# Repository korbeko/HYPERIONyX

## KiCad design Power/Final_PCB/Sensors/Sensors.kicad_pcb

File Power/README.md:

When loading the KiCad project, the components directory must be adjusted based on where you copy the repository.
To fix:
1. Select configure paths in the project window.
2. Select name: COMPONENTS and click folder icon to change the path to wherever the components folder is.

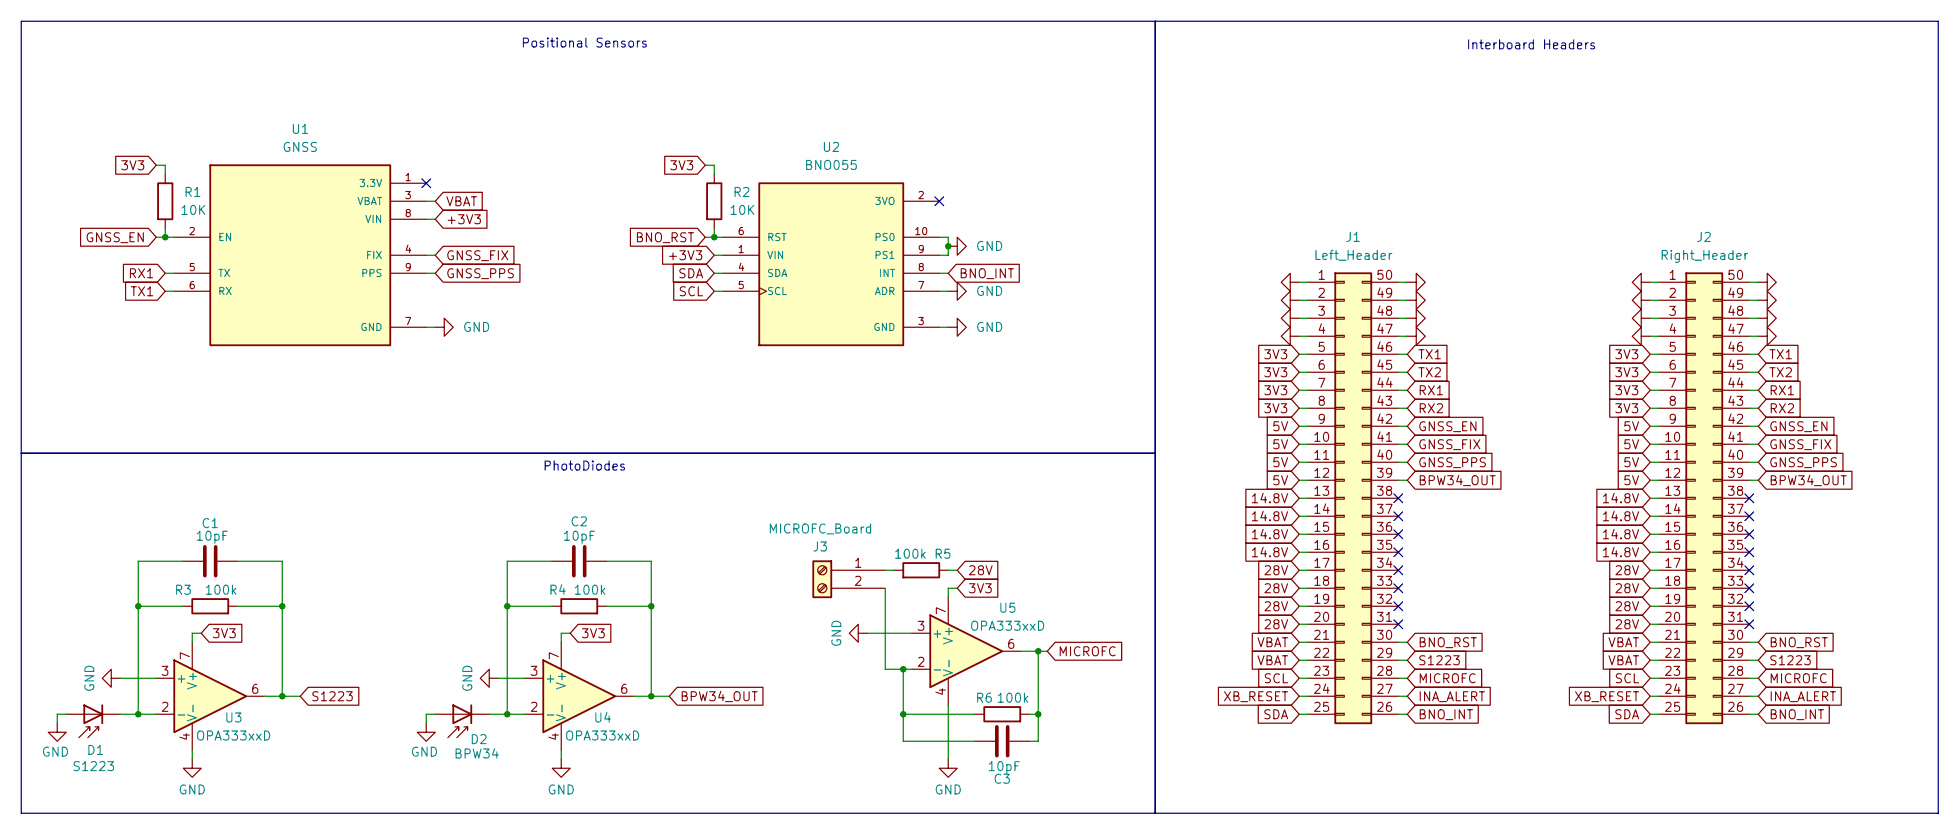
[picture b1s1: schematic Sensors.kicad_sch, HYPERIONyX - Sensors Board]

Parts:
C1, C2, C3: 10pF; C_Disc_D3.0mm_W1.6mm_P2.50mm
D1: S1223; PinHeader_1x02_P2.54mm_Vertical
D2: BPW34; PinHeader_1x02_P2.54mm_Vertical
J1: Left_Header; PinHeader_2x25_P2.54mm_Vertical
J2: Right_Header; PinHeader_2x25_P2.54mm_Vertical
J3: MICROFC_Board; PinHeader_1x02_P2.54mm_Vertical
R1, R2: 10K; R_Axial_DIN0207_L6.3mm_D2.5mm_P7.62mm_Horizontal
R3, R4, R5, R6: 100k; R_Axial_DIN0207_L6.3mm_D2.5mm_P7.62mm_Horizontal
U1: GNSS; PARTREV 2022-12-01
U2: BNO055; PARTREV N/A
U3, U4, U5: OPA333xxD; SOIC-8_3.9x4.9mm_P1.27mm

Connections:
3V3: J1.5, J1.6, J1.7, J1.8, J2.5, J2.6, J2.7, J2.8, R1.1, R2.1, U3.7 (V+), U4.7 (V+), U5.7 (V+)
5V: J1.9, J1.10, J1.11, J1.12, J2.9, J2.10, J2.11, J2.12
14.8V: J1.13, J1.14, J1.15, J1.16, J2.13, J2.14, J2.15, J2.16
28V: J1.17, J1.18, J1.19, J1.20, J2.17, J2.18, J2.19, J2.20, R5.1
+3V3: U1.8 (VIN), U2.1 (VIN)
BNO_INT: J1.26, J2.26, U2.8 (INT)
BNO_RST: J1.30, J2.30, R2.2, U2.6 (RST)
BPW34_OUT: C2.1, J1.39, J2.39, R4.2, U4.6
GND: D1.2 (A), D2.2 (A), J1.1, J1.2, J1.3, J1.4, J1.47, J1.48, J1.49, J1.50, J2.1, J2.2, J2.3, J2.4, J2.47, J2.48, J2.49, J2.50, U1.7 (GND), U2.3 (GND), U2.7 (ADR), U2.9 (PS1), U2.10 (PS0), U3.3 (+), U3.4 (V-), U4.3 (+), U4.4 (V-), U5.3 (+), U5.4 (V-)
GNSS_EN: J1.42, J2.42, R1.2, U1.2 (EN)
GNSS_FIX: J1.41, J2.41, U1.4 (FIX)
GNSS_PPS: J1.40, J2.40, U1.9 (PPS)
INA_ALERT: J1.27, J2.27
MICROFC: C3.1, J1.28, J2.28, R6.2, U5.6
unnamed: C1.2, D1.1 (K), R3.1, U3.2 (-)
unnamed: C2.2, D2.1 (K), R4.1, U4.2 (-)
unnamed: C3.2, J3.2 (SOUT), R6.1, U5.2 (-)
unnamed: J3.1 (VBIAS), R5.2
RX1: J1.44, J2.44, U1.5 (TX)
RX2: J1.43, J2.43
S1223: C1.1, J1.29, J2.29, R3.2, U3.6
SCL: J1.23, J2.23, U2.5 (SCL)
SDA: J1.25, J2.25, U2.4 (SDA)
TX1: J1.46, J2.46, U1.6 (RX)
TX2: J1.45, J2.45
VBAT: J1.21, J1.22, J2.21, J2.22, U1.3 (VBAT)
XB_RESET: J1.24, J2.24

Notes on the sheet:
Interboard Headers
Positional Sensors
PhotoDiodes

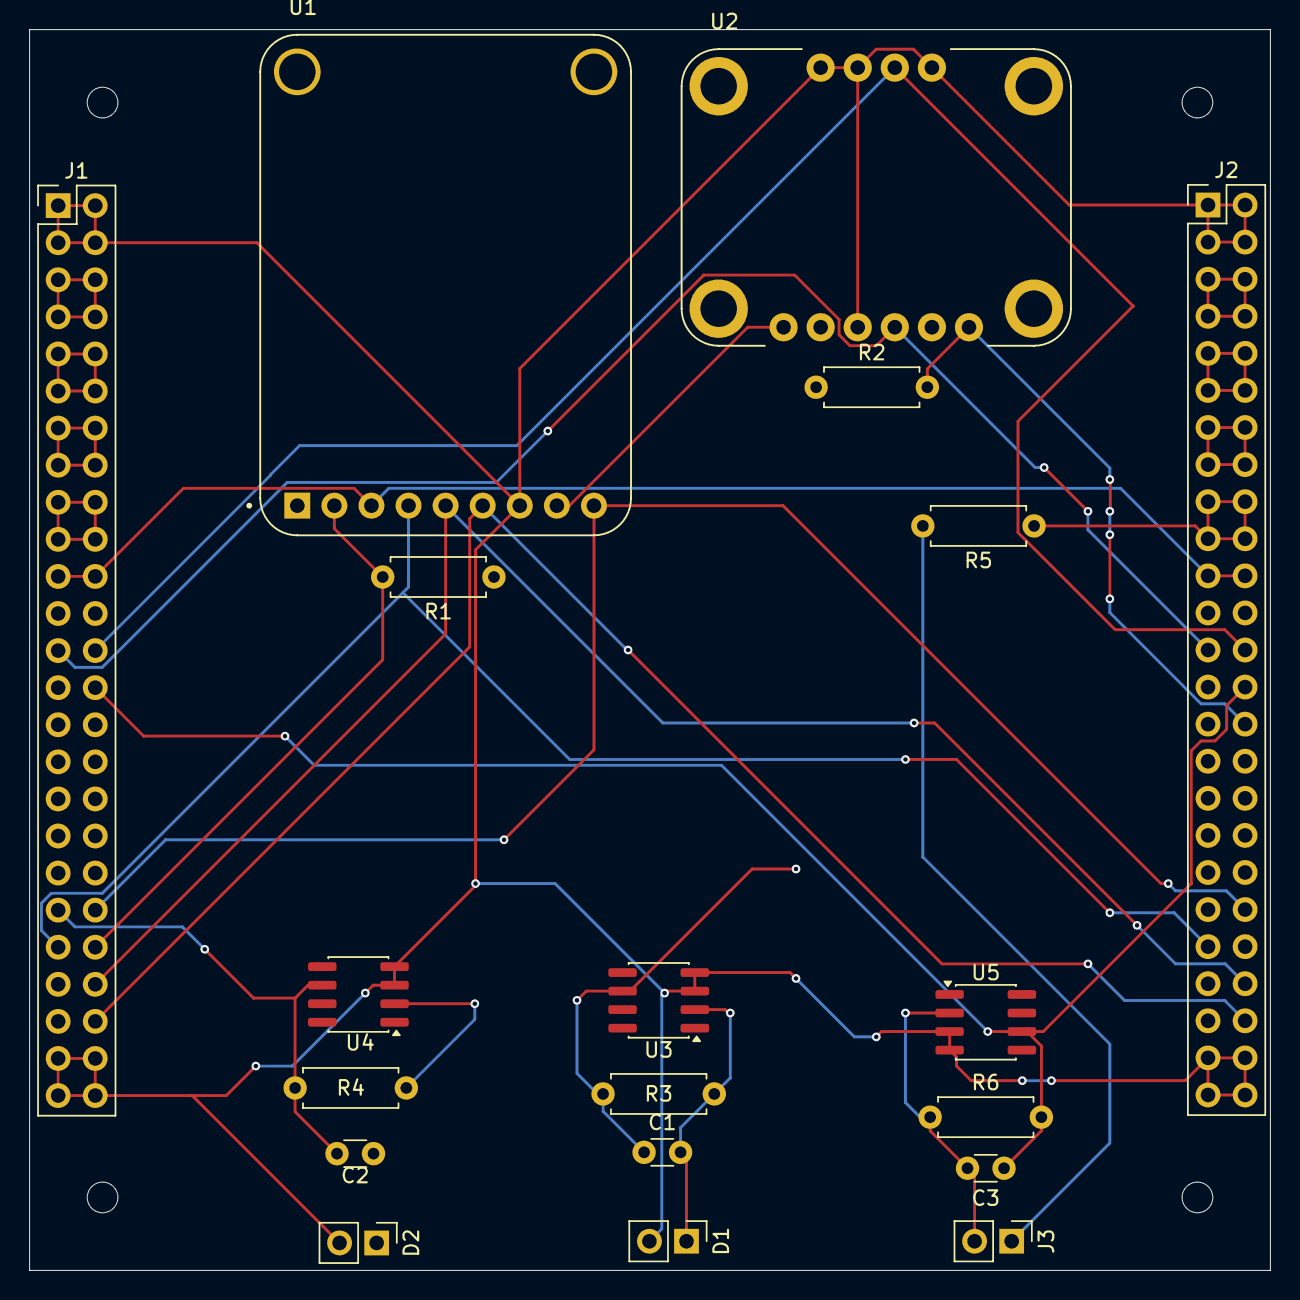
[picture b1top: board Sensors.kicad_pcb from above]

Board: 4 copper layers, 85.0 x 85.0 mm, 20 parts (1 on the bottom side), 27 nets.

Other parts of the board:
.: .; LOGO

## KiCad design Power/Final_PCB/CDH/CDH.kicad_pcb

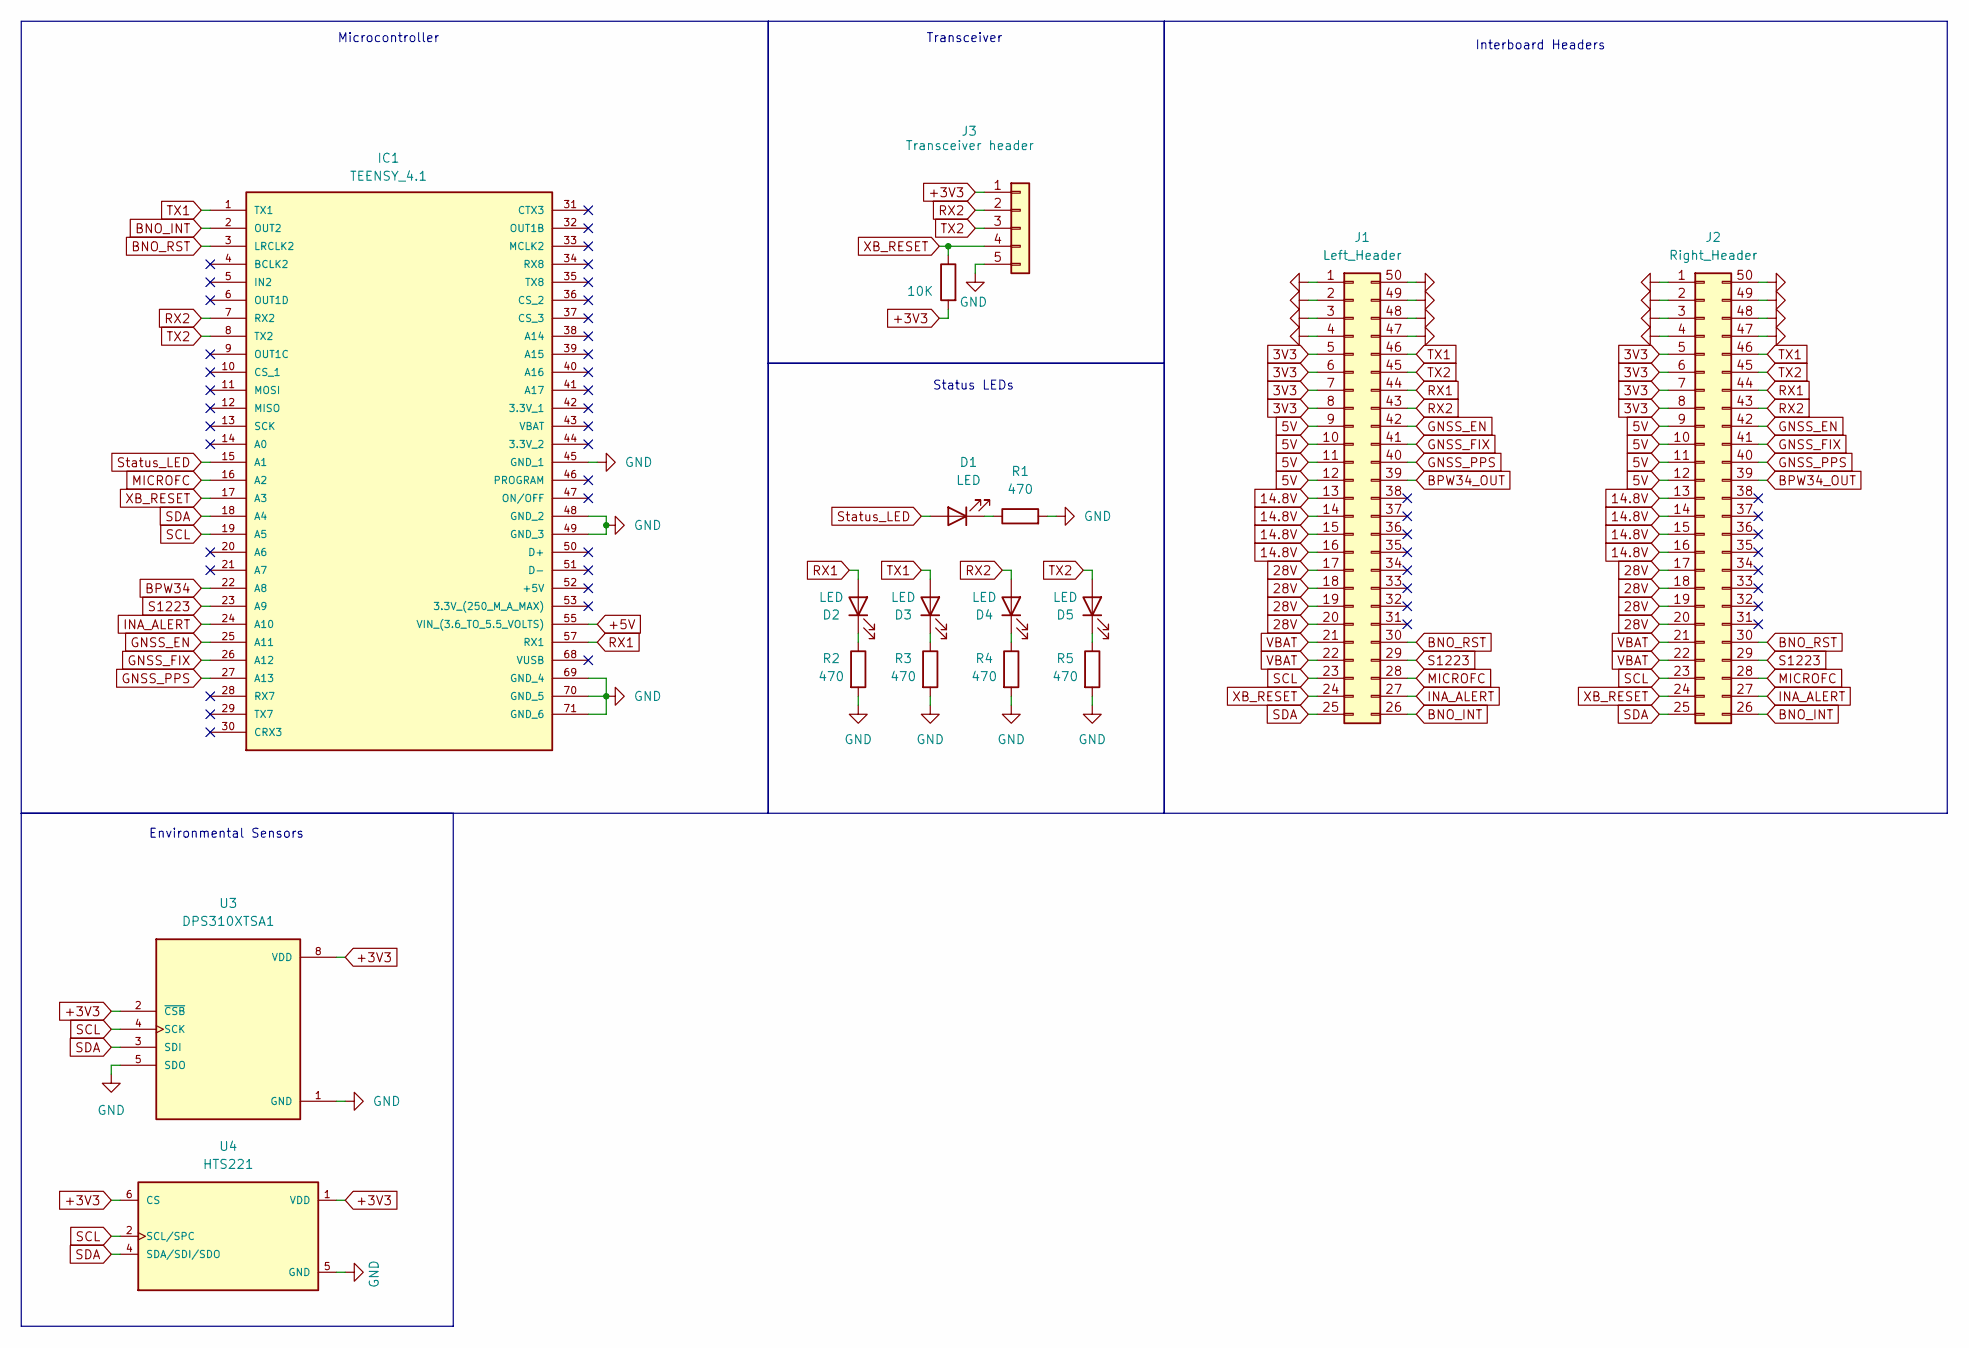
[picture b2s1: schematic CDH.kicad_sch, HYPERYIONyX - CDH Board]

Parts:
D1, D2, D3, D4, D5: LED; LED_D3.0mm
IC1: TEENSY_4.1; TEENSY41; Manufacturer_Part_Number TEENSY 4.1
J1: Left_Header; PinHeader_2x25_P2.54mm_Vertical
J2: Right_Header; PinHeader_2x25_P2.54mm_Vertical
J3: Transceiver header; PinHeader_1x05_P2.54mm_Vertical
R1, R2, R3, R4, R5: 470; R_Axial_DIN0207_L6.3mm_D2.5mm_P7.62mm_Horizontal
R10: 10K; R_Axial_DIN0207_L6.3mm_D2.5mm_P7.62mm_Horizontal
U3: DPS310XTSA1; DPS310_Breakout
U4: HTS221; HTS221_Breakout; PARTREV Rev 1

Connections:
3V3: J1.5, J1.6, J1.7, J1.8, J2.5, J2.6, J2.7, J2.8
5V: J1.9, J1.10, J1.11, J1.12, J2.9, J2.10, J2.11, J2.12
14.8V: J1.13, J1.14, J1.15, J1.16, J2.13, J2.14, J2.15, J2.16
28V: J1.17, J1.18, J1.19, J1.20, J2.17, J2.18, J2.19, J2.20
+3V3: J3.1, R10.2, U3.2 (~CSB), U3.8 (VDD), U4.1 (VDD), U4.6 (CS)
+5V: IC1.55 (VIN_(3.6_TO_5.5_VOLTS))
BNO_INT: IC1.2 (OUT2), J1.26, J2.26
BNO_RST: IC1.3 (LRCLK2), J1.30, J2.30
BPW34: IC1.22 (A8)
BPW34_OUT: J1.39, J2.39
GND: IC1.45 (GND_1), IC1.48 (GND_2), IC1.49 (GND_3), IC1.69 (GND_4), IC1.70 (GND_5), IC1.71 (GND_6), J1.1, J1.2, J1.3, J1.4, J1.47, J1.48, J1.49, J1.50, J2.1, J2.2, J2.3, J2.4, J2.47, J2.48, J2.49, J2.50, J3.5, R1.2, R2.2, R3.2, R4.2, R5.2, U3.1 (GND), U3.5 (SDO), U4.5 (GND)
GNSS_EN: IC1.25 (A11), J1.42, J2.42
GNSS_FIX: IC1.26 (A12), J1.41, J2.41
GNSS_PPS: IC1.27 (A13), J1.40, J2.40
INA_ALERT: IC1.24 (A10), J1.27, J2.27
MICROFC: IC1.16 (A2), J1.28, J2.28
unnamed: D1.1 (K), R1.1
unnamed: D2.1 (K), R2.1
unnamed: D3.1 (K), R3.1
unnamed: D4.1 (K), R4.1
unnamed: D5.1 (K), R5.1
RX1: D2.2 (A), IC1.57 (RX1), J1.44, J2.44
RX2: D4.2 (A), IC1.7 (RX2), J1.43, J2.43, J3.2
S1223: IC1.23 (A9), J1.29, J2.29
SCL: IC1.19 (A5), J1.23, J2.23, U3.4 (SCK), U4.2 (SCL/SPC)
SDA: IC1.18 (A4), J1.25, J2.25, U3.3 (SDI), U4.4 (SDA/SDI/SDO)
Status_LED: D1.2 (A), IC1.15 (A1)
TX1: D3.2 (A), IC1.1 (TX1), J1.46, J2.46
TX2: D5.2 (A), IC1.8 (TX2), J1.45, J2.45, J3.3
VBAT: J1.21, J1.22, J2.21, J2.22
XB_RESET: IC1.17 (A3), J1.24, J2.24, J3.4, R10.1

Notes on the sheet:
Interboard Headers
Microcontroller
Environmental Sensors
Status LEDs
Transceiver

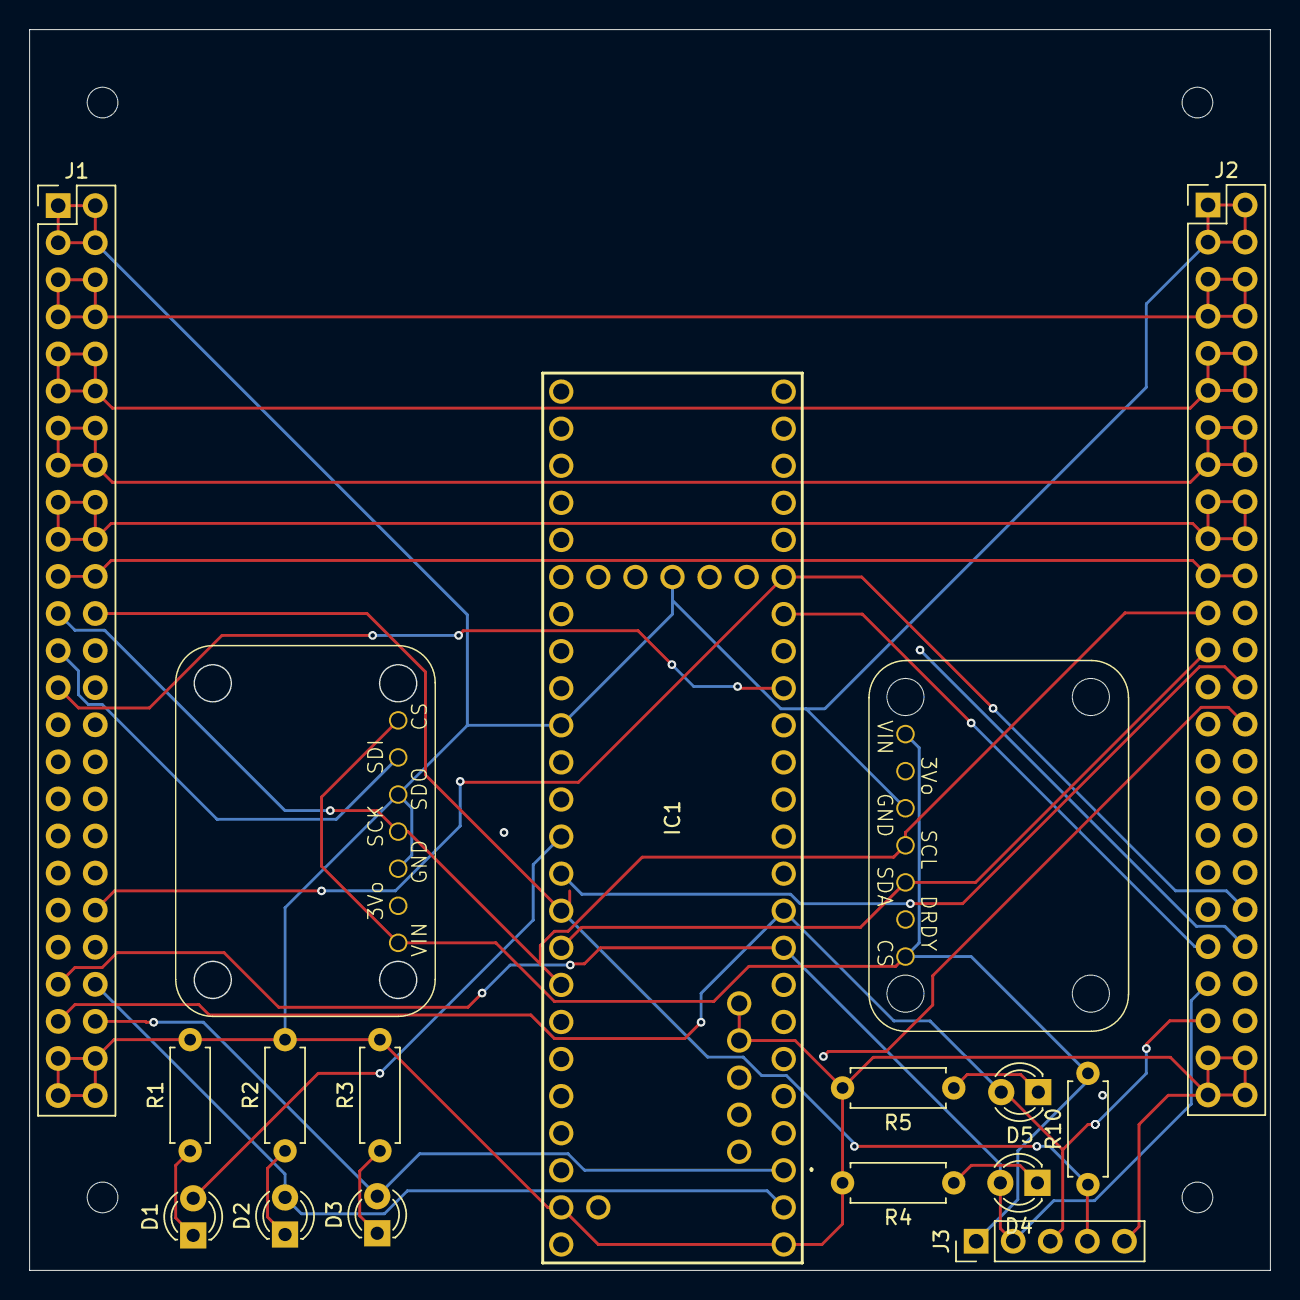
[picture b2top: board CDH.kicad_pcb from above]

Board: 4 copper layers, 84.9 x 84.9 mm, 18 parts (1 on the bottom side), 29 nets.

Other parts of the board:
.: .; LOGO

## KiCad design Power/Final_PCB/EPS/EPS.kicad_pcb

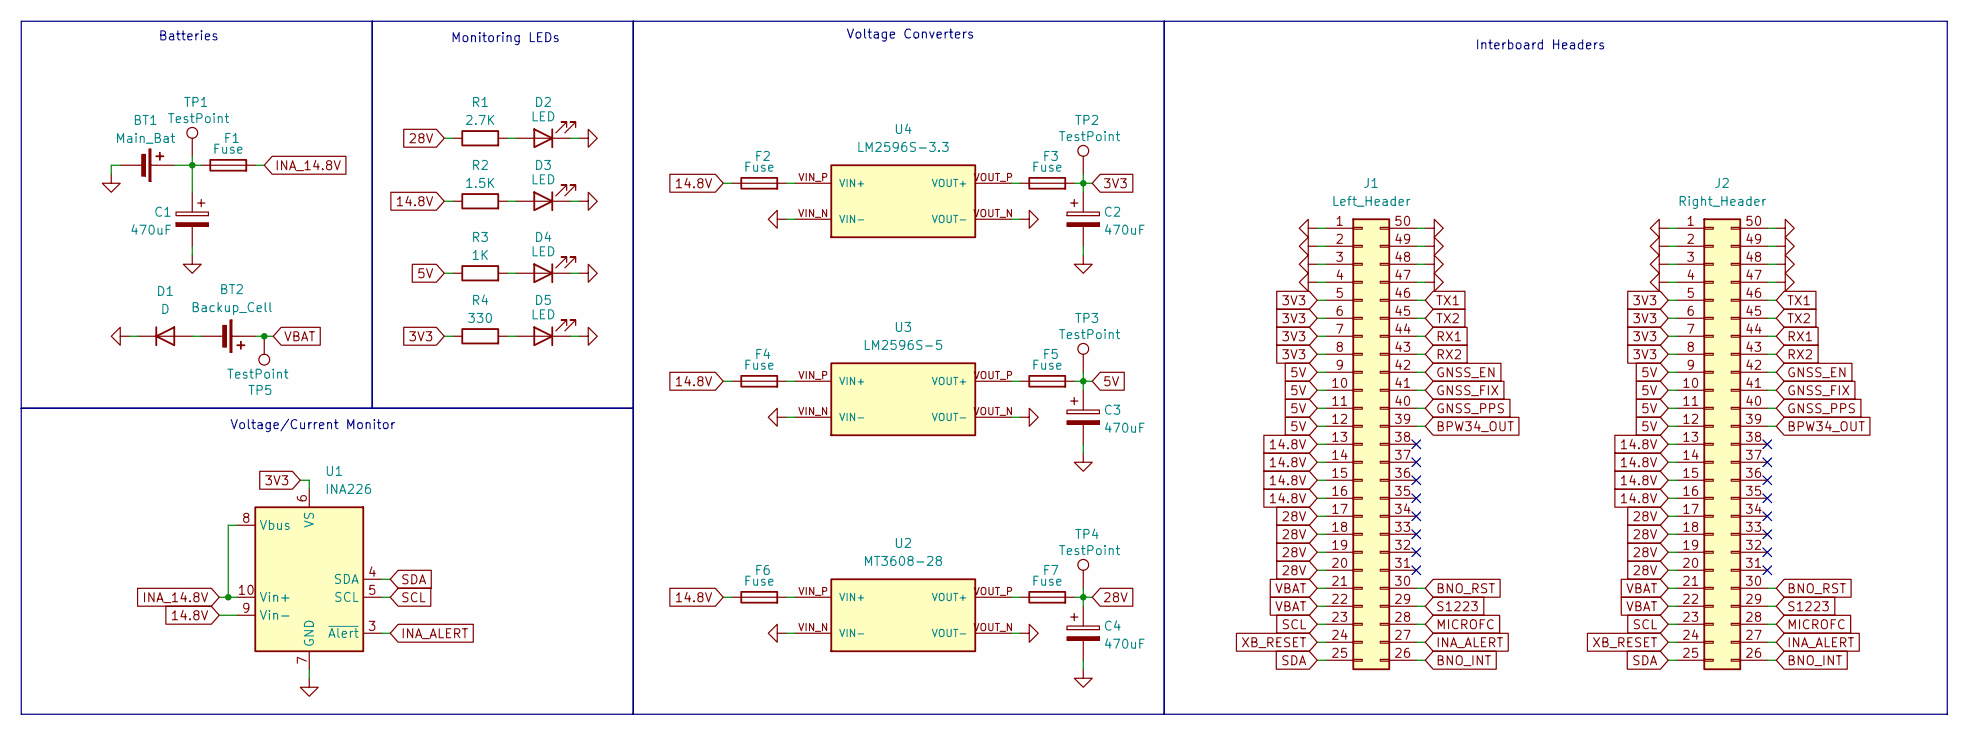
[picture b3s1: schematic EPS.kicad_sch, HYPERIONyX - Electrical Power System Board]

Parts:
BT1: Main_Bat; PinHeader_1x02_P2.54mm_Vertical
BT2: Backup_Cell; BatteryHolder_Multicomp_BC-2001_1x2032
C1, C2, C3, C4: 470uF; CP_Radial_D8.0mm_P3.50mm
D1: D; D_DO-15_P10.16mm_Horizontal
D2, D3, D4, D5: LED; LED_D3.0mm
F1, F2, F3, F4, F5, F6, F7: Fuse; Fuse_Blade_Mini_directSolder
J1: Left_Header; PinHeader_2x25_P2.54mm_Vertical
J2: Right_Header; PinHeader_2x25_P2.54mm_Vertical
R1: 2.7K; R_Axial_DIN0207_L6.3mm_D2.5mm_P7.62mm_Horizontal
R2: 1.5K; R_Axial_DIN0207_L6.3mm_D2.5mm_P7.62mm_Horizontal
R3: 1K; R_Axial_DIN0207_L6.3mm_D2.5mm_P7.62mm_Horizontal
R4: 330; R_Axial_DIN0207_L6.3mm_D2.5mm_P7.62mm_Horizontal
TP1, TP2, TP3, TP4, TP5: TestPoint; TestPoint_Loop_D2.50mm_Drill1.0mm
U1: INA226; INA_Breakout
U2: MT3608-28; MODULE_MT3608_DC-DC_STEP_UP_CONVERTER_2A_BOOSTER_MODULE
U3: LM2596S-5; LM2596_Breakout
U4: LM2596S-3.3; LM2596_Breakout

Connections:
3V3: C2.1, F3.2, J1.5, J1.6, J1.7, J1.8, J2.5, J2.6, J2.7, J2.8, R4.1, TP2.1 (1_1), U1.6 (VS)
5V: C3.1, F5.2, J1.9, J1.10, J1.11, J1.12, J2.9, J2.10, J2.11, J2.12, R3.1, TP3.1 (1_1)
14.8V: F2.1, F4.1, F6.1, J1.13, J1.14, J1.15, J1.16, J2.13, J2.14, J2.15, J2.16, R2.1, U1.9 (Vin-)
28V: C4.1, F7.2, J1.17, J1.18, J1.19, J1.20, J2.17, J2.18, J2.19, J2.20, R1.1, TP4.1 (1_1)
BNO_INT: J1.26, J2.26
BNO_RST: J1.30, J2.30
BPW34_OUT: J1.39, J2.39
GND: BT1.2 (-), C1.2, C2.2, C3.2, C4.2, D1.1 (K), D2.1 (K), D3.1 (K), D4.1 (K), D5.1 (K), J1.1, J1.2, J1.3, J1.4, J1.47, J1.48, J1.49, J1.50, J2.1, J2.2, J2.3, J2.4, J2.47, J2.48, J2.49, J2.50, U1.7 (GND), U2.VIN_N (VIN-), U2.VOUT_N (VOUT-), U3.VIN_N (VIN-), U3.VOUT_N (VOUT-), U4.VIN_N (VIN-), U4.VOUT_N (VOUT-)
GNSS_EN: J1.42, J2.42
GNSS_FIX: J1.41, J2.41
GNSS_PPS: J1.40, J2.40
INA_14.8V: F1.2, U1.8 (Vbus), U1.10 (Vin+)
INA_ALERT: J1.27, J2.27, U1.3 (~Alert)
MICROFC: J1.28, J2.28
unnamed: BT1.1 (+), C1.1, F1.1, TP1.1 (1_1)
unnamed: BT2.2 (-), D1.2 (A)
unnamed: D2.2 (A), R1.2
unnamed: D3.2 (A), R2.2
unnamed: D4.2 (A), R3.2
unnamed: D5.2 (A), R4.2
unnamed: F6.2, U2.VIN_P (VIN+)
unnamed: F7.1, U2.VOUT_P (VOUT+)
unnamed: F4.2, U3.VIN_P (VIN+)
unnamed: F5.1, U3.VOUT_P (VOUT+)
unnamed: F2.2, U4.VIN_P (VIN+)
unnamed: F3.1, U4.VOUT_P (VOUT+)
RX1: J1.44, J2.44
RX2: J1.43, J2.43
S1223: J1.29, J2.29
SCL: J1.23, J2.23, U1.5 (SCL)
SDA: J1.25, J2.25, U1.4 (SDA)
TX1: J1.46, J2.46
TX2: J1.45, J2.45
VBAT: BT2.1 (+), J1.21, J1.22, J2.21, J2.22, TP5.1 (1_1)
XB_RESET: J1.24, J2.24

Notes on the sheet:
Voltage Converters
Voltage/Current Monitor
Monitoring LEDs
Batteries
Interboard Headers

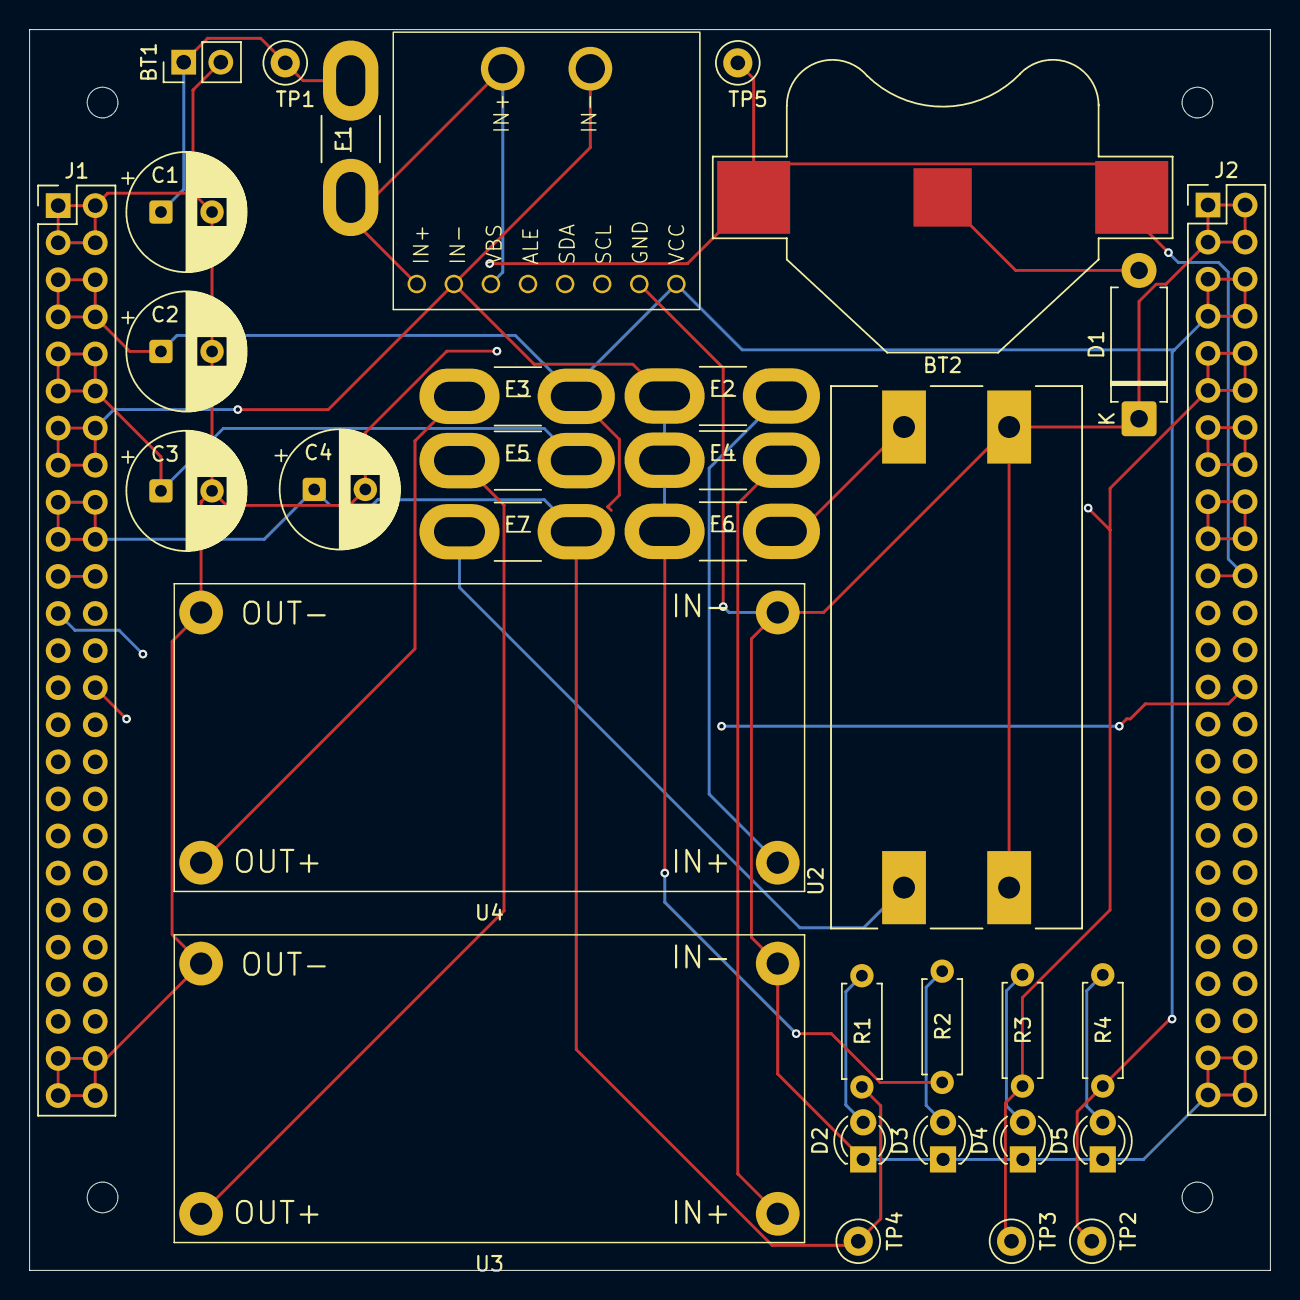
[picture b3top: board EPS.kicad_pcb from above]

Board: 4 copper layers, 85.0 x 85.0 mm, 34 parts (1 on the bottom side), 35 nets.

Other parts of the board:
.: .; LOGO

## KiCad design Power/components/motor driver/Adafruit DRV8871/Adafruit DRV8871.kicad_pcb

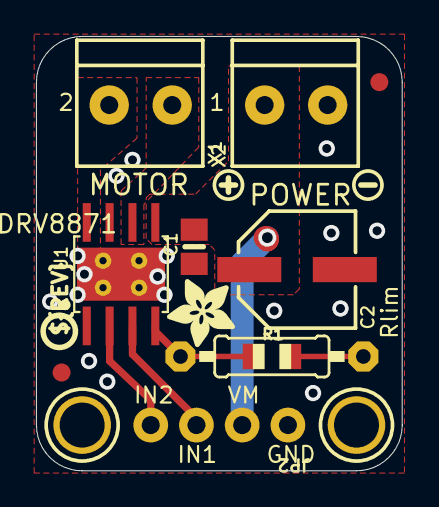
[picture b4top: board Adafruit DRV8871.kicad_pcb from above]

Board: 2 copper layers, 20.3 x 24.1 mm, 15 parts (0 on the bottom side), 7 nets.

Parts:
C1: 0.1uF/50V; 0805-NO
C2: 22uF/63V; PANASONIC_D
FID1, FID2: FIDUCIAL""; FIDUCIAL_1MM
JP2: 1X04_ROUND_76
R1: 30K; 0805-THM
U1: DRV8871; HSOP8
U$9, U$10: MOUNTINGHOLE2.5; MOUNTINGHOLE_2.5_PLATED
U$11: SYMBOL_PLUS
U$12: SYMBOL_MINUS
U$14: ADAFRUIT_3.5MM
U$15: PCBFEAT-REV-040
X1: DCMOTOR; TERMBLOCK_1X2-3.5MM
X2: POWER; TERMBLOCK_1X2-3.5MM

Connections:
GND: C1.2, C2.-, JP2.1, R1.1, U1.1, U1.7, U1.GND, U1.P$1, U1.P$2, U1.P$3, U1.P$4, X2.2
IN1: JP2.3, U1.3
IN2: JP2.4, U1.2
unnamed: R1.2, U1.4
OUT1: U1.6, X1.2
OUT2: U1.8, X1.1
VMOTOR: C1.1, C2.+, JP2.2, U1.5, X2.1

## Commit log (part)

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2026-02-18 Completed Electrical Schematic
2026-02-24 Finalised PCB Schematic with missing components
2026-02-24 Added missing motor driver component
2026-02-27 Create README for CDH
2026-02-27 SSFSF Framework added (Service Layer)
2026-03-03 Adjusted photodiodes & added missing components
2026-03-03 Minor EPS changes
2026-03-04 Wed 04/03
2026-05-16 Updated PCB
2026-05-17 Adjusted EPS for CCA
2026-06-06 Added HTS221
